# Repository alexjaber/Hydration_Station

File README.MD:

# Hydration Station Electrical and Embedded software

This GitHub repository holds the KiCad files for the Hydration Station circuit board and the embedded software running on the Nano and the ESP32.

# Electrical Overview

A majority of the electrical design is in the circuit board. This board was designed in KiCad. To open the project, open KiCad and use KiCad to open the `Full Hydration Station.kicad\_pro` in the `Hydration Station Circuit` folder. This will allow you open up the schematic and PCB layout for the Hydration Station circuit board.

The design focuses on using two microcontroller breakout boards: the Arduino Nano and ESP32 board. The Arduino Nano handles control of the solenoids through the MOSFETs as well as the LCD display through I2C, and the ESP32 handles communication with the website. The two boards communicate with each other through I2C. This link is primarily used so the Arduino can tell the ESP32 when bottles get cleaned, filled, etc. and then gets forwarded to the website through HTTP requests.

There are a number of sensors, which all have corresponding 2.54mm header breakouts connecting to either the ESP32 or the Arduino. These include a weight sensor for soap level detection, a LCD for interfacing with the user, buttons for interacting with the Hydration Station, a water flow sensor, and a hall effect sensor for detecting when the door is closed.

# Software Overview

Currently, the code for the Arduino Nano is the only one that has been implemented. This code implements a simple state machine to handle cleaning. Work still needs to be done on the software side to get the sensors working, getting the ESP32 connected with the website, and getting the two microcontrollers communicating with each other.

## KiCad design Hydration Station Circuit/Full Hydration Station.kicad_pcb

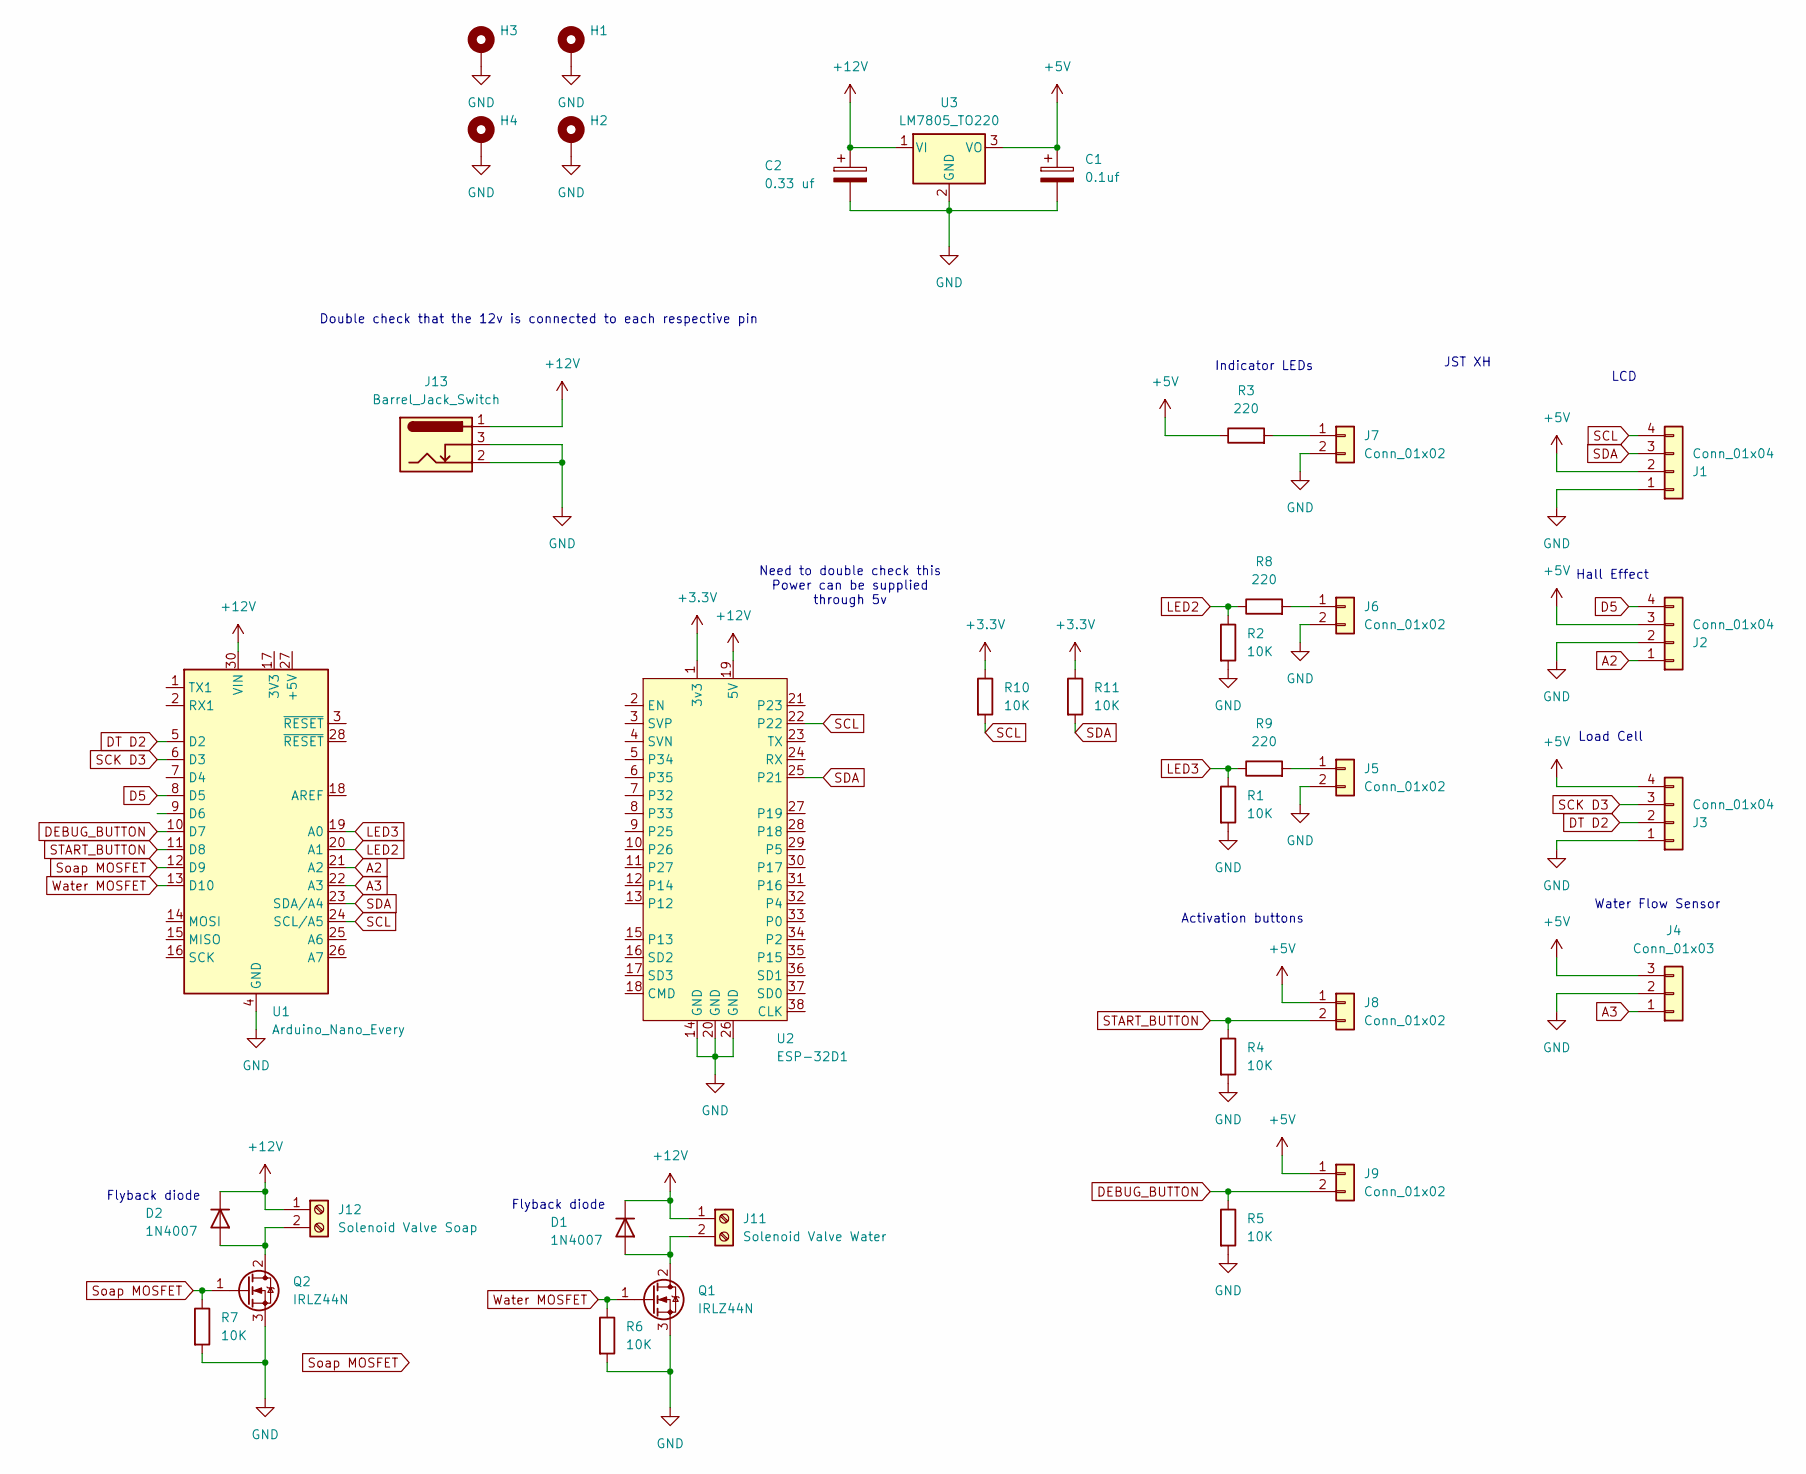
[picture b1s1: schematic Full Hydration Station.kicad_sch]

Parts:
C1: 0.1uf; CP_Radial_D4.0mm_P1.50mm
C2: 0.33 uf; CP_Radial_D4.0mm_P1.50mm
D1, D2: 1N4007; D_DO-41_SOD81_P10.16mm_Horizontal
ESP-32D1: U2; ESP32
H1, H2, H3, H4: MountingHole_Pad; MountingHole_4.3mm_M4_DIN965_Pad_TopBottom
J1, J2, J3: Conn_01x04; PinHeader_1x04_P2.54mm_Vertical
J4: Conn_01x03; PinHeader_1x03_P2.54mm_Vertical
J5, J6, J7, J8, J9: Conn_01x02; PinHeader_1x02_P2.54mm_Vertical
J11: Solenoid Valve Water; TerminalBlock_TE_282834-2_1x02_P2.54mm_Horizontal
J12: Solenoid Valve Soap; TerminalBlock_TE_282834-2_1x02_P2.54mm_Horizontal
J13: Barrel_Jack_Switch; BarrelJack_GCT_DCJ200-10-A_Horizontal
Q1, Q2: IRLZ44N; TO-220-3_Vertical
R1, R2, R4, R5, R6, R7, R10, R11: 10K; R_Axial_DIN0207_L6.3mm_D2.5mm_P7.62mm_Horizontal
R3, R8, R9: 220; R_Axial_DIN0207_L6.3mm_D2.5mm_P7.62mm_Horizontal
U1: Arduino_Nano_Every; Arduino_Nano
U3: LM7805_TO220; TO-220-3_Vertical

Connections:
+3.3V: ESP-32D1.1 (3v3), R10.1, R11.1
+5V: C1.1, J1.2, J2.3, J3.4, J4.3, J8.1, J9.1, R3.1, U3.3 (VO)
+12V: C2.1, D1.1 (K), D2.1 (K), ESP-32D1.19 (5V), J11.1, J12.1, J13.1, U1.30 (VIN), U3.1 (VI)
A2: J2.1, U1.21 (A2)
A3: J4.1, U1.22 (A3)
D5: J2.4, U1.8 (D5)
DEBUG_BUTTON: J9.2, R5.1, U1.10 (D7)
DT D2: J3.2, U1.5 (D2)
GND: C1.2, C2.2, ESP-32D1.14 (GND), ESP-32D1.20 (GND), ESP-32D1.26 (GND), H1.1, H2.1, H3.1, H4.1, J1.1, J2.2, J3.1, J4.2, J5.2, J6.2, J7.2, J13.2, J13.3, Q1.3 (S), Q2.3 (S), R1.2, R2.2, R4.2, R5.2, R6.2, R7.2, U1.4 (GND), U1.29 (GND), U3.2 (GND)
LED2: R2.1, R8.1, U1.20 (A1)
LED3: R1.1, R9.1, U1.19 (A0)
unnamed: D1.2 (A), J11.2, Q1.2 (D)
unnamed: D2.2 (A), J12.2, Q2.2 (D)
unnamed: J5.1, R9.2
unnamed: J6.1, R8.2
unnamed: J7.1, R3.2
SCK D3: J3.3, U1.6 (D3)
SCL: ESP-32D1.22, J1.4, R10.2, U1.24 (SCL/A5)
SDA: ESP-32D1.25 (P21), J1.3, R11.2, U1.23 (SDA/A4)
START_BUTTON: J8.2, R4.1, U1.11 (D8)
Soap MOSFET: Q2.1 (G), R7.1, U1.12 (D9)
Water MOSFET: Q1.1 (G), R6.1, U1.13 (D10)

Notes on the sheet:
Water Flow Sensor
Activation buttons
Load Cell
Hall Effect
JST XH
Need to double check this Power can be supplied through 5v
Indicator LEDs
LCD
Flyback diode
Double check that the 12v is connected to each respective pin

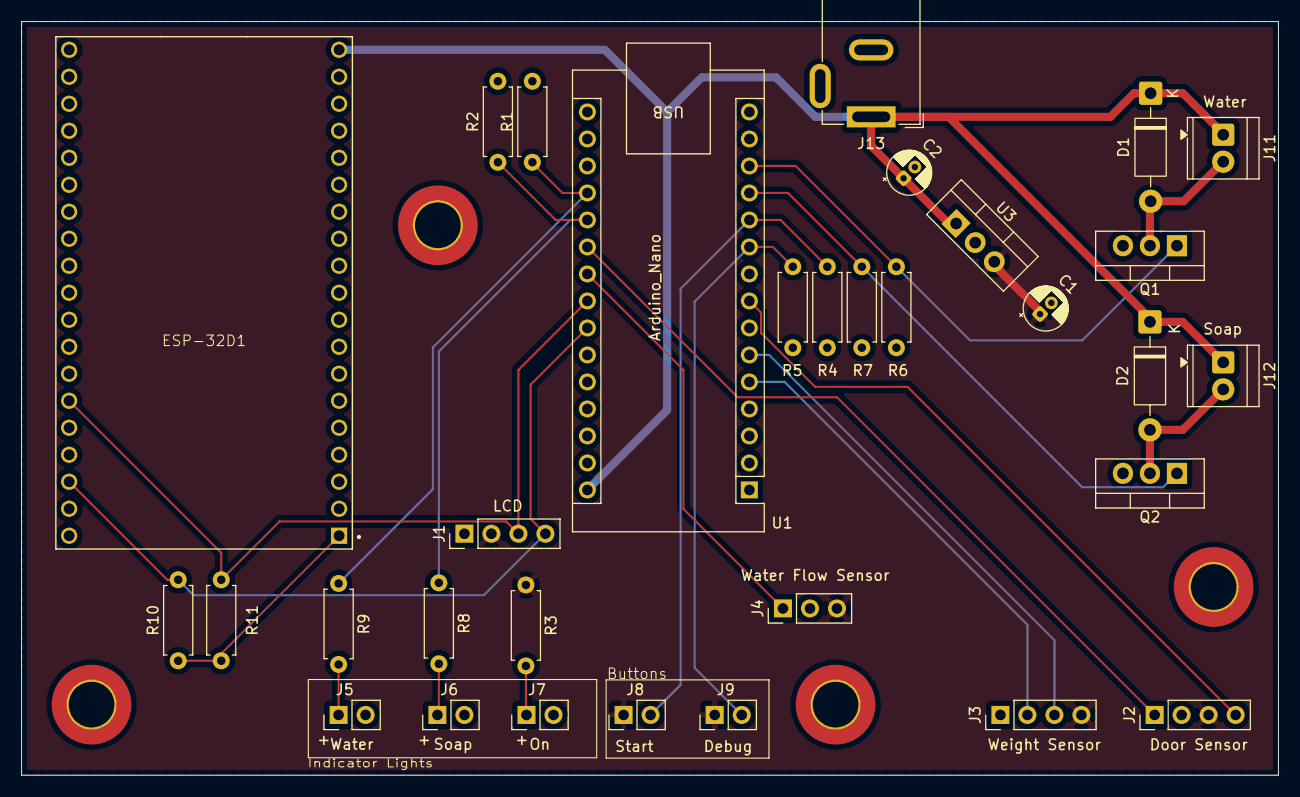
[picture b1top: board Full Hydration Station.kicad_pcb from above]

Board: 2 copper layers, 118.3 x 70.9 mm, 36 parts (0 on the bottom side), 22 nets.
